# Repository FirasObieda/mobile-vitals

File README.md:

# Mobile Vitals: AI-Powered Health Tracker with ML Predictions & Alerts

Senior Design Project — Department of Computer Engineering, University of Sharjah
(Fall 2025–2026)

**Team:** Majid M. Almheiri · Firas Obieda Abu-Bader · Abdullah Kaddoura
**Supervisor:** Dr. Bassel Soudan

## Overview

Chronic conditions like hypertension, hypoxemia, and heart-rate irregularities are
hard to catch early because the standard measurement tools (cuffs, pulse oximeters)
are manual, invasive, and non-continuous. **Mobile Vitals** is a wearable device that
continuously and non-invasively estimates **heart rate (HR), blood pressure (BP), and
blood oxygen saturation (SpO₂)** from a PPG (photoplethysmography) signal, streams
the data to the cloud, runs it through a trained ML model, and alerts the user through
a companion mobile app when a reading falls outside a normal range.

## How it works

1. A compact ESP32-based wearable captures PPG, skin temperature, and motion data.
2. Readings are sent over **Bluetooth** to the mobile app (Wi-Fi on the wearable
   proved unreliable in practice, so the design was changed to Bluetooth
   wearable↔phone, Wi-Fi phone↔cloud).
3. The app double-buffers readings and uploads them to **Firebase Firestore** every
   ~10 seconds.
4. A Firebase Cloud Function preprocesses the signal and runs it through a trained
   **Random Forest** model (selected after comparing Random Forest, XGBoost, and
   LightGBM) to predict HR, systolic/diastolic BP, and SpO₂.
5. Predictions are written back to Firestore and shown live in the app; abnormal
   readings trigger a two-tier (yellow/red) alert.

## Repository structure

```
firmware/     ESP32 (Arduino) firmware — sensor capture & Bluetooth transmission
backend/      Firebase Cloud Function (Python) that runs the ML inference model
mobile-app/   Flutter/FlutterFlow app — pairing, live vitals, history, alerts
ml/ppg-bp/    ML pipeline trained on the PPG-BP dataset (superseded, kept for reference)
ml/ptt-ppg/   ML pipeline trained on the PTT-PPG dataset — the one used in the final model
hardware/     KiCad PCB design files for the wearable
```

## Hardware

| Component | Model | Purpose |
|---|---|---|
| Microcontroller | Seeed Studio XIAO ESP32-C3 | Main processing unit |
| PPG sensor | MAX30105 | Captures the PPG waveform used for inference |
| Temperature sensor | MLX90614 | Contactless skin temperature (IR) |
| IMU | LSM6DS3 | Motion/orientation, for motion-artifact handling |
| Display | Waveshare 1.69" LCD | Shows HR, SpO₂, temperature, BP |
| Power | 3.7V 800mAh Li-Po + TP4056 charger | Portable power + USB charging |
| Enclosure | Custom 3D-printed casing (Onshape) | Protection & wearability |

Communication between sensors uses I²C/SPI on the wearable; wearable↔phone is
Bluetooth; phone↔cloud is Wi-Fi.

## Machine learning

Two datasets were evaluated:

- **PPG-BP** (Figshare, 657 segments / 219 subjects) — initial results were weak
  (best overall MAE ≈ 7.1, from XGBoost) and the dataset was judged not reliable
  enough.
- **PTT PPG** (PhysioNet, 22 subjects, 3,233 records across sit/run/walk) — much
  stronger results. **Random Forest** gave the best overall performance: SBP R² ≈
  0.955, DBP R² ≈ 0.921, HR R² ≈ 0.827, SpO₂ R² ≈ 0.845, overall MAE ≈ 1.31.

Preprocessing pipeline: linear interpolation for gaps → Butterworth low-pass filter
(15 Hz, 8th order) → Savitzky–Golay smoothing → normalization to [0,1] →
segmentation into 10-second windows.

## Software specifications

| Tool / Library | Version | Purpose |
|---|---|---|
| Arduino IDE | 2.3.2 | Firmware upload for the XIAO ESP32-C3 |
| Pandas | 2.2.3 | Data cleaning/manipulation |
| NumPy | 1.26.4 | Numerical computation |
| SciPy | 1.13.1 | Filtering & feature extraction |
| scikit-learn | 1.4.2 | Model training/evaluation |
| Joblib | 1.4.2 | Model persistence |
| firebase-admin (Python) | 6.4.0 | Cloud Function ↔ Firebase access |
| functions-framework | 3.6.0 | Serves the Python Cloud Function |
| cloudevents | 1.11.0 | Event handling for Cloud Functions |

## Setup

Each subfolder has more detail — start here:

- **Firmware:** open `firmware/ESP32_SOURCE_CODE.ino` in the Arduino IDE with the
  ESP32 board package installed.
- **Backend:** see the Backend section below and `backend/functions/requirements.txt`.
  Requires your own Firebase service account key (not included — see Configuration note).
- **Mobile app:** see `mobile-app/README.md`.
- **ML pipelines:** open the notebooks under `ml/ppg-bp/` or `ml/ptt-ppg/` in Jupyter.
- **Hardware:** open `hardware/wearable_device_sdp.kicad_pro` in KiCad.

### Backend (`backend/`)
```bash
cd backend/functions
python -m venv venv
source venv/bin/activate   # venv\Scripts\activate on Windows
pip install -r requirements.txt
```
This uses the Firebase Admin SDK, which needs a service account key that is **not
included** in this repo:
1. Firebase console → Project Settings → Service Accounts → Generate new private key.
2. Save it locally and point `GOOGLE_APPLICATION_CREDENTIALS` at it.
3. Never commit this file (it's covered by `.gitignore`).

Deploy: `firebase deploy --only functions` from `backend/`.

## Configuration note

This repo doesn't include environment-specific credentials (Firebase service
account key, API keys) — that's standard practice for any public repo. See the
Backend and `mobile-app/README.md` sections for how to supply your own.

## Project report

The full SDP2 report (architecture rationale, literature review, testing, and
results in detail) is available separately and covers material summarized above,
including the design evolution from the SDP1 proposal (dual PPG sensors → single
MAX30105; BME280 → MLX90614; Wi-Fi → Bluetooth for the wearable link; breadboard →
custom PCB).

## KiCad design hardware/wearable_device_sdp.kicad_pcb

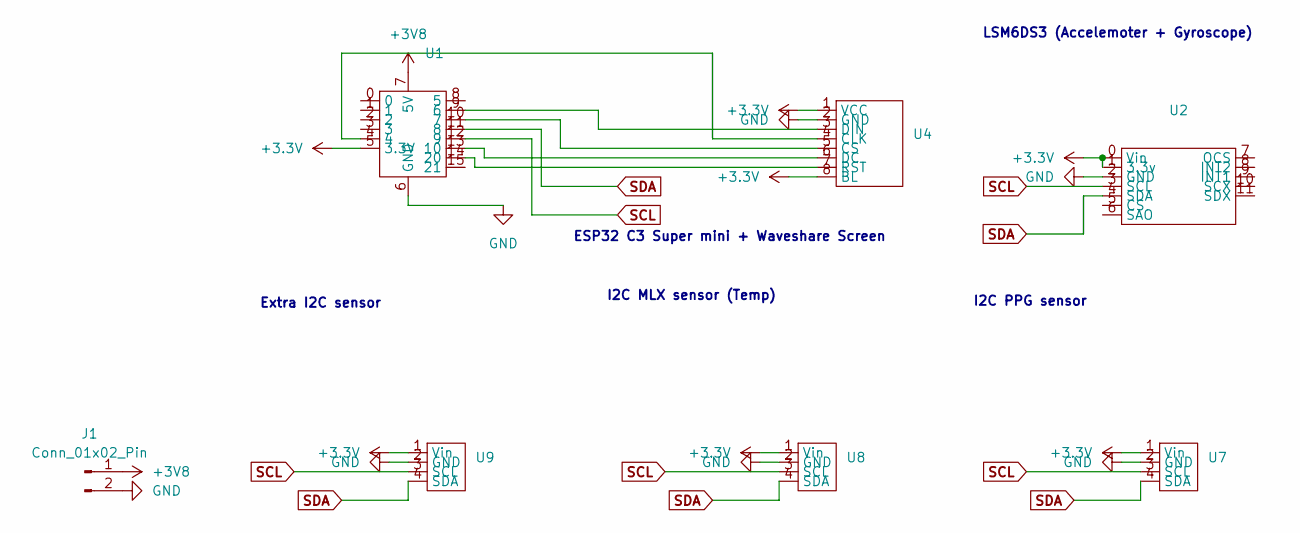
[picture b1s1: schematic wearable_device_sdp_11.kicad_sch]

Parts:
J1: Conn_01x02_Pin; PinHeader_1x02_P2.54mm_Vertical
U1: ESP32_C3_SuperMini_Flipped
U2: LSM6DS3
U4: PinHeader_1x08_P2.54mm_Vertical
U7, U9: PinHeader_1x04_P2.54mm_Vertical
U8: MLX_Temp_Sensor

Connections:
+3.3V: U1.5 (3.3V), U2.0 (Vin), U2.1 (3.3v), U4.1 (VCC), U4.8 (BL), U7.1 (Vin), U8.1 (Vin), U9.1 (Vin)
+3V8: J1.1, U1.7 (5V)
GND: J1.2, U1.6 (GND), U2.2 (GND), U4.2 (GND), U7.2 (GND), U8.2 (GND), U9.2 (GND)
unnamed: U1.9 (6), U4.3 (DIN)
unnamed: U1.10 (7), U4.5 (CS)
unnamed: U1.13 (10), U4.6 (DC)
unnamed: U1.14 (20), U4.7 (RST)
unnamed: U1.4, U4.4 (CLK)
SCL: U1.12 (9), U2.3 (SCL), U7.3 (SCL), U8.3 (SCL), U9.3 (SCL)
SDA: U1.11 (8), U2.4 (SDA), U7.4 (SDA), U8.4 (SDA), U9.4 (SDA)

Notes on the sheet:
Extra I2C sensor
I2C MLX sensor (Temp)
ESP32 C3 Super mini + Waveshare Screen
I2C PPG sensor
LSM6DS3 (Accelemoter + Gyroscope)

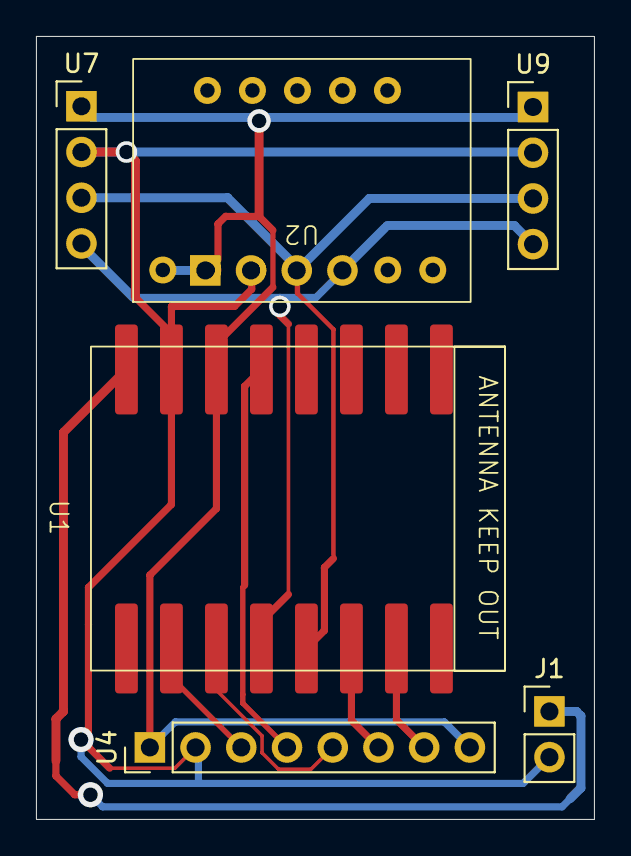
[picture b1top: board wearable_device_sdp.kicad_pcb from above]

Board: 2 copper layers, 31.0 x 43.5 mm, 7 parts (1 on the bottom side), 10 nets.
